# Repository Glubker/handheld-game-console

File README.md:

# Handheld Game Console

A personal project documenting the design and build of a fully custom 
handheld game console from scratch. This repository contains all source 
code, PCB design files, and supporting materials for the build. It is 
not a polished open source project, but a record of something I built 
for myself that others are welcome to learn from and adapt.

The current build runs on a Radxa Rock 5C with an 8" 1280x800 display, 
housed in a custom 3D printed casing with a custom PCB handling all 
physical input. The graphical interface and game launcher were written 
entirely from scratch in Flutter. Physical buttons are mapped to standard 
keypresses by a dedicated background program, meaning any software that 
accepts keyboard input runs on the device without modification.

Full documentation covering the hardware, PCB, software architecture, 
OS configuration, and complete build process is available at  
**[lubker.dk/gameconsole](https://lubker.dk/gameconsole)**

---

## Repository Structure

    handheld-game-console/
    ├── pcb/                          # KiCad PCB design files and Gerbers
    ├── raspberry-pi/                 # Original build: Raspberry Pi 4 + C++/Raylib
    │   ├── game_console/             # Main interface and built-in games
    │   │   ├── main.cpp
    │   │   ├── src/                  # UI components and utilities
    │   │   ├── resources/            # Fonts and icons
    │   │   └── games/game_src/       # Source for built-in games
    │   │       ├── pong/
    │   │       ├── dodgers/
    │   │       ├── flappy_bird/
    │   │       ├── pacman/
    │   │       └── platformer/
    │   ├── gpio_testing.py           # GPIO input testing script (gpiozero)
    │   └── gpio_to_keypress.c        # Input handler (WiringPi)
    └── radxa-rock-5c/                # Current build: Radxa Rock 5C + Flutter
        ├── flutter_src/              # Flutter interface source
        │   └── lib/
        │       ├── main.dart
        │       ├── models/           # Game model, keyboard manager, settings
        │       ├── screens/          # Home screen
        │       ├── widgets/          # UI components
        │       └── utils/
        ├── gpio_testing.py           # GPIO input testing script (gpiod)
        ├── gpio_to_keypress.c        # Input handler (libgpiod)
        └── launcher.sh               # Launch script

---

## License

MIT. See [LICENSE](LICENSE) for details.

If you use this project as a reference or build upon it, a credit or link 
back to [lubker.dk/gameconsole](https://lubker.dk/gameconsole) is appreciated.

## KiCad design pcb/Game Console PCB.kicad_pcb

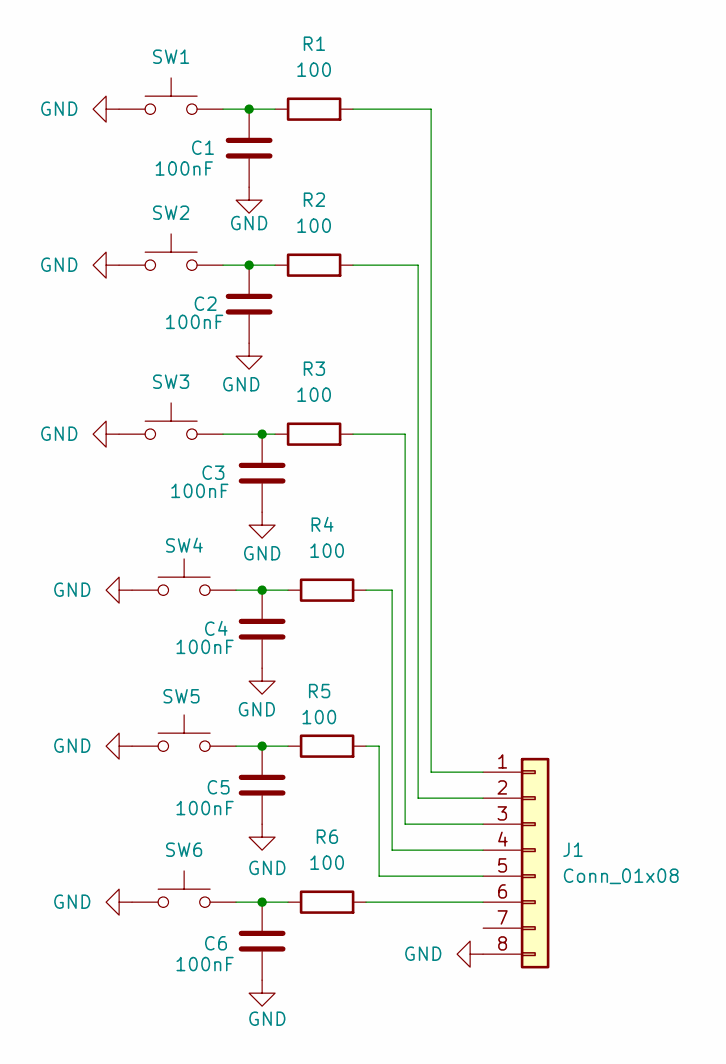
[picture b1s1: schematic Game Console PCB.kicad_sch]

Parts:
C1, C2, C3, C4, C5, C6: 100nF; C_0805_2012Metric_Pad1.18x1.45mm_HandSolder
J1: Conn_01x08; JST_EH_B8B-EH-A_1x08_P2.50mm_Vertical
R1, R2, R3, R4, R5, R6: 100; R_0805_2012Metric_Pad1.20x1.40mm_HandSolder
SW1, SW2, SW3, SW4, SW5, SW6: SW_Omron_B3FS; TactSwitch 3x4x2

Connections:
GND: C1.1, C2.1, C3.1, C4.1, C5.1, C6.1, J1.8, SW1.1, SW2.1, SW3.1, SW4.1, SW5.1, SW6.1
unnamed: C1.2, R1.1, SW1.2
unnamed: C2.2, R2.1, SW2.2
unnamed: C3.2, R3.1, SW3.2
unnamed: C4.2, R4.1, SW4.2
unnamed: C5.2, R5.1, SW5.2
unnamed: C6.2, R6.1, SW6.2
unnamed: J1.1, R1.2
unnamed: J1.2, R2.2
unnamed: J1.3, R3.2
unnamed: J1.4, R4.2
unnamed: J1.5, R5.2
unnamed: J1.6, R6.2

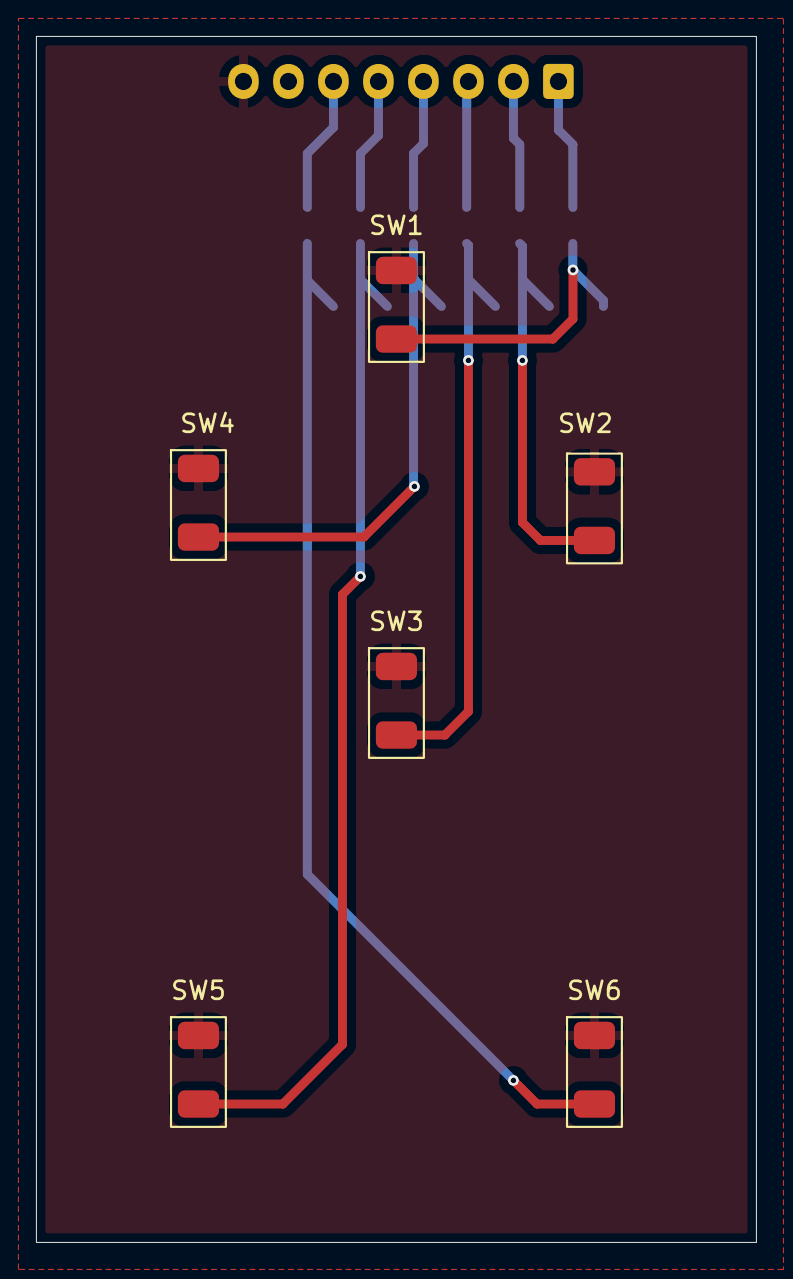
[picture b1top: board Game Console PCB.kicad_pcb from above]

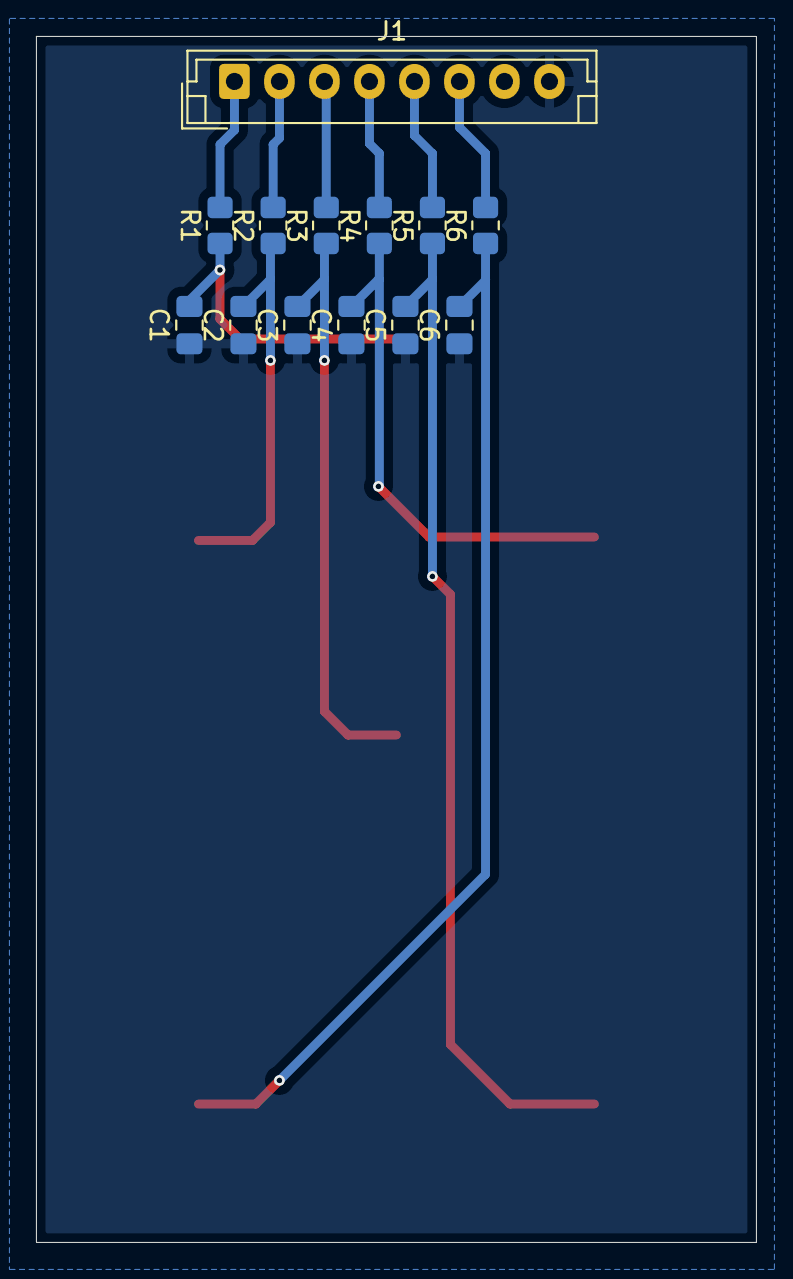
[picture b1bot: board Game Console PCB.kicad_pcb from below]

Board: 2 copper layers, 40.0 x 67.0 mm, 19 parts (13 on the bottom side), 13 nets.

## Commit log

2026-04-25 Rename build folders to raspberry-pi and radxa-rock-5c
2026-04-26 Remove old code and keep necessary includes
2026-04-27 Add image of rebuilt game console
    Added an image of the rebuilt game console to the README.
2026-04-27 Remove photo from README
    Removed image from README.md
